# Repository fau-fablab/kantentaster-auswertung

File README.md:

kantentaster-auswertung
=======================

##motivation
Initially CNC mills do not "know" where the material is.
If you want to mill through the material, you have to know exactly where your material is relatively to the machine coordinate system.

For this the typical tool is a 3D probe.
However this probe cannot simply be connected to the controller of the mill.
This project is a Schmitt-triggered current loop to adapt the probe to the controller.

##circuit
The typical design for such a 3D probe (in our case a Renishaw) is that you have a contact which opens upon touching something with the tip of the probe.
When not touching anything the resistance of the probe is in the range of 20k.
When touching something the resistance becomes very large.

To have a robust measurement this circuit uses a current loop.
It consists of a constant-current-source which constantly puts a current of 1mA through the sensor.
Attached to this circuit is a Schmitt-trigger.
The hysteresis levels are configurable, because the trigger has to be fine tuned "in field".

Finally the output is separated from the controller with an optocoupler, because the sensor cable runs through a potentially rough environment.

----------------------
##version history
The first version of the PCB is in directory ```kantentaster_platine```. This version did not work. A complete redesign and current development version is in ```kantentaster_v2```.

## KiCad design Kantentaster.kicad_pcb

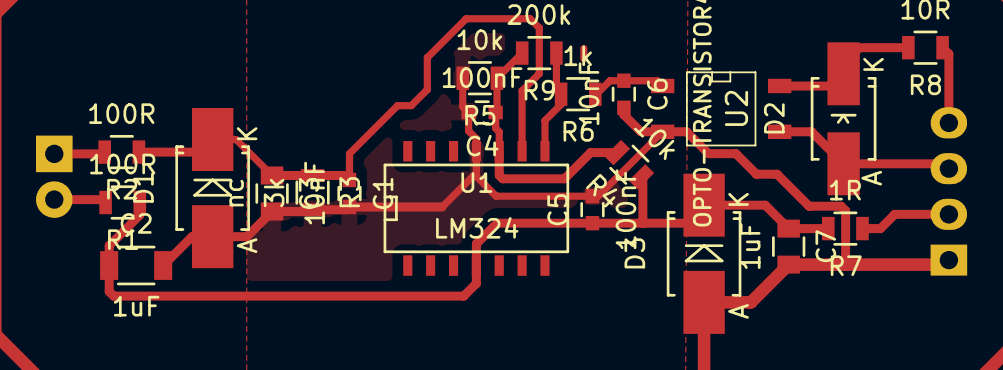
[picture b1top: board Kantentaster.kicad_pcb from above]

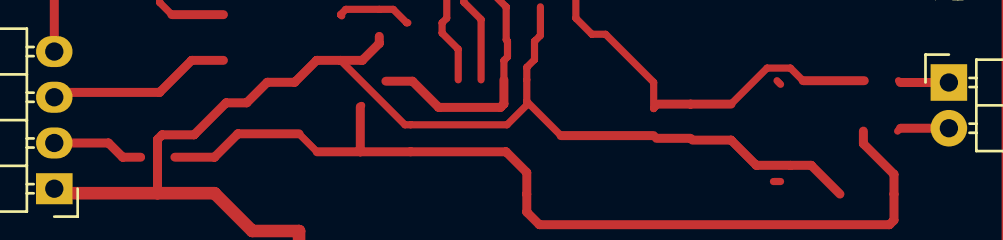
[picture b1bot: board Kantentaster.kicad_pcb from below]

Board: 2 copper layers, 23 parts (2 on the bottom side), 12 nets.

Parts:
C1, C6: 10nF; C_0603
C2: 1uF; C_1206
C3: nc; C_0805
C4, C5: 100nF; C_0603
C7: 1uF; C_0805
D1: ZENER_15V; Diode-SMB_Handsoldering
D2: ZENER_15V; Diode-SMA_Handsoldering
D3: ZENER_18V; Diode-SMB_Handsoldering
P1: Anschluss Kantentaster; Pin_Header_Angled_1x02
P2: CONN_01X04; Pin_Header_Angled_1x04
R1, R2: 100R; R_0805
R3: 3k; R_0805
R4, R5: 10k; R_0805
R6: 1k; R_0805
R7: 1R; R_0805
R8: 10R; R_0805
R9: 200k; R_0805
U1: LM324; SOIC-14_N
U2: OPTO-TRANSISTOR4; SO-4

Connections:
+12V: C2.1, C5.1, C7.1, D3.2, R1.1, R4.1, R7.2, U1.4
GND: C1.2, C2.2, C3.2, C4.2, C5.2, C6.2, C7.2, D1.1, D3.1, P2.1, R3.2, R5.2, U1.11, U2.2
unnamed: C1.1, C3.1, D1.2, R2.1, R3.1, U1.9
unnamed: C4.1, R4.2, R5.1, R9.2, U1.10
unnamed: C6.1, R6.1, U2.1
unnamed: D2.1, P2.3, U2.3
unnamed: D2.2, R8.2, U2.4
unnamed: P1.1, R2.2
unnamed: P1.2, R1.2
unnamed: P2.2, R7.1
unnamed: P2.4, R8.1
unnamed: R6.2, R9.1, U1.8

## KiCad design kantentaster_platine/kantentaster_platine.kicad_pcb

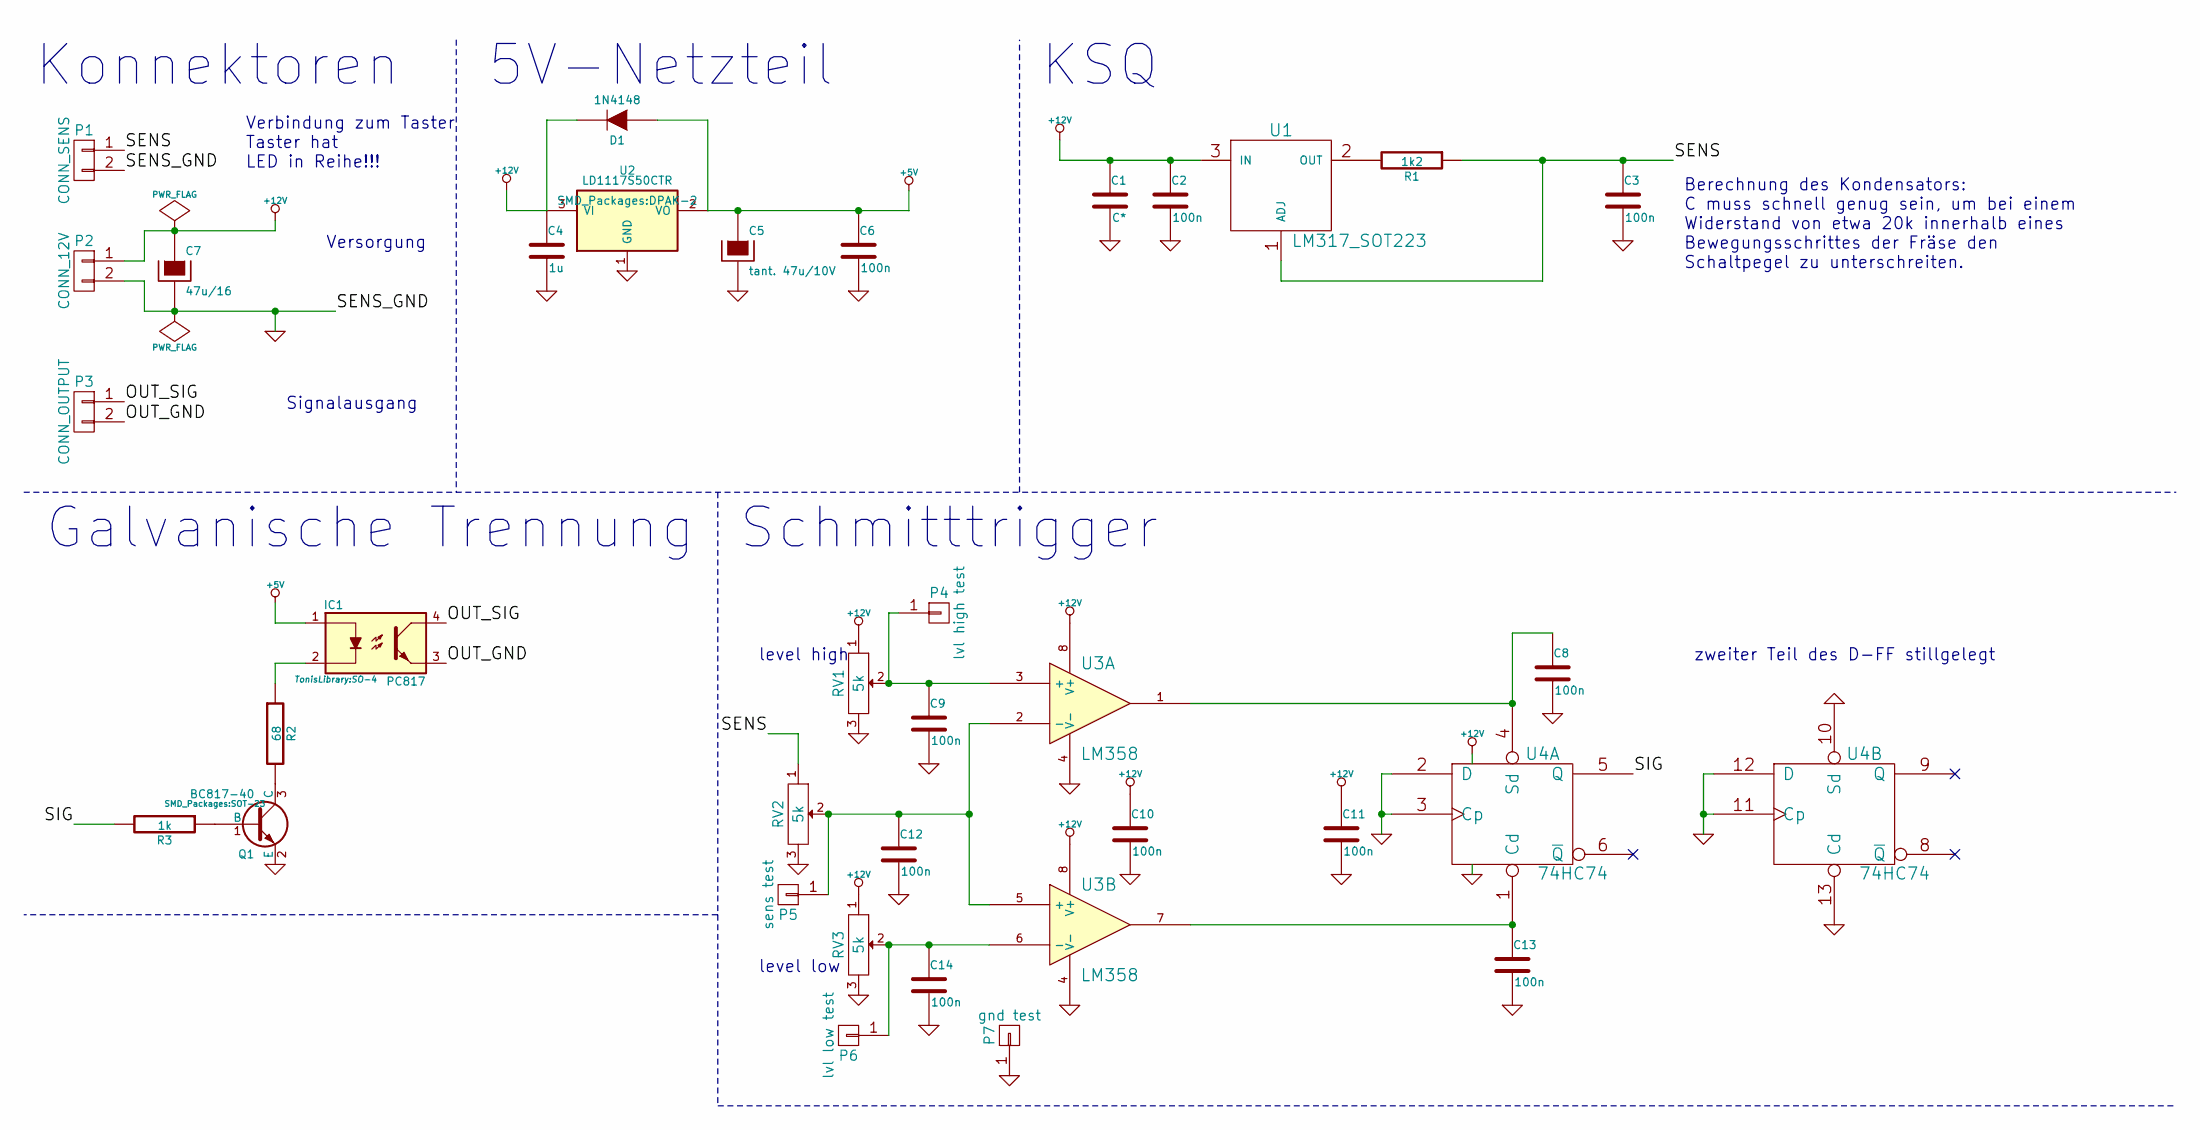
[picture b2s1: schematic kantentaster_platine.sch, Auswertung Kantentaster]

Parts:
C1: C*; C_0805
C2, C3, C6, C8, C9, C10, C11, C12, C13, C14: 100n; C_0805
C4: 1u; C_0805
C5: tant. 47u/10V; TantalC_SizeD_EIA-7343_Reflow
C7: 47u/16; c_elec_6.3x7.7
D1: 1N4148; Diode-MiniMELF_Standard
IC1: PC817; SO-4
P1: CONN_SENS; AK300-2
P2: CONN_12V; AK300-2
P3: CONN_OUTPUT; AK300-2
P4: lvl high test; Measurement_Point_Round-SMD-Pad_Big
P5: sens test; Measurement_Point_Round-SMD-Pad_Big
P6: lvl low test; Measurement_Point_Round-SMD-Pad_Big
P7: gnd test; Measurement_Point_Round-SMD-Pad_Big
Q1: BC817-40; SOT-23
R1: 1k2; SMD-0805
R2: 68; SMD-0805
R3: 1k; SMD-0805
RV1, RV2, RV3: 5k; Potentiometer_WirePads_Small
U1: LM317_SOT223; SOT-223
U2: LD1117S50CTR; DPAK-2
U3: LM358; DIP-8__300_ELL
U4: 74HC74; SOIC-14_W

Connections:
+5V: C5.1, C6.1, D1.1 (A), IC1.1, U2.2 (VO)
+12V: C1.1, C2.1, C4.1, C7.1, C10.1, C11.1, D1.2 (K), P2.1, RV1.1, RV3.1, U1.3 (IN), U2.3 (VI), U3.8 (V+), U4.14 (VCC)
/OUT_GND: IC1.3, P3.2
/OUT_SIG: IC1.4, P3.1
/SENS: C3.1, P1.1, R1.1, RV2.1, U1.1 (ADJ)
/SIG: R3.2, U4.5 (Q)
GND: C1.2, C2.2, C3.2, C4.2, C5.2, C6.2, C7.2, C8.2, C9.2, C10.2, C11.2, C12.2, C13.2, C14.2, P1.2, P2.2, P7.1, Q1.2 (E), RV1.3, RV2.3, RV3.3, U2.1 (GND), U3.4 (V-), U4.2 (D), U4.3 (Cp), U4.7 (GND), U4.10 (Sd), U4.11 (Cp), U4.12 (D), U4.13 (Cd)
unnamed: C8.1, U3.1, U4.4 (Sd)
unnamed: C9.1, P4.1, RV1.2, U3.3 (+)
unnamed: C12.1, P5.1, RV2.2, U3.2 (-), U3.5 (+)
unnamed: C13.1, U3.7, U4.1 (Cd)
unnamed: C14.1, P6.1, RV3.2, U3.6 (-)
unnamed: IC1.2, R2.1
unnamed: Q1.1 (B), R3.1
unnamed: Q1.3 (C), R2.2
unnamed: R1.2, U1.2 (OUT)

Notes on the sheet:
Konnektoren
5V-Netzteil
KSQ
Galvanische Trennung
Schmitttrigger
Verbindung zum Taster Taster hat LED in Reihe!!!
Versorgung
Signalausgang
level low
level high
zweiter Teil des D-FF stillgelegt
Berechnung des Kondensators: C muss schnell genug sein, um bei einem Widerstand von etwa 20k innerhalb eines Bewegungsschrittes der Fräse den Schaltpegel zu unterschreiten.

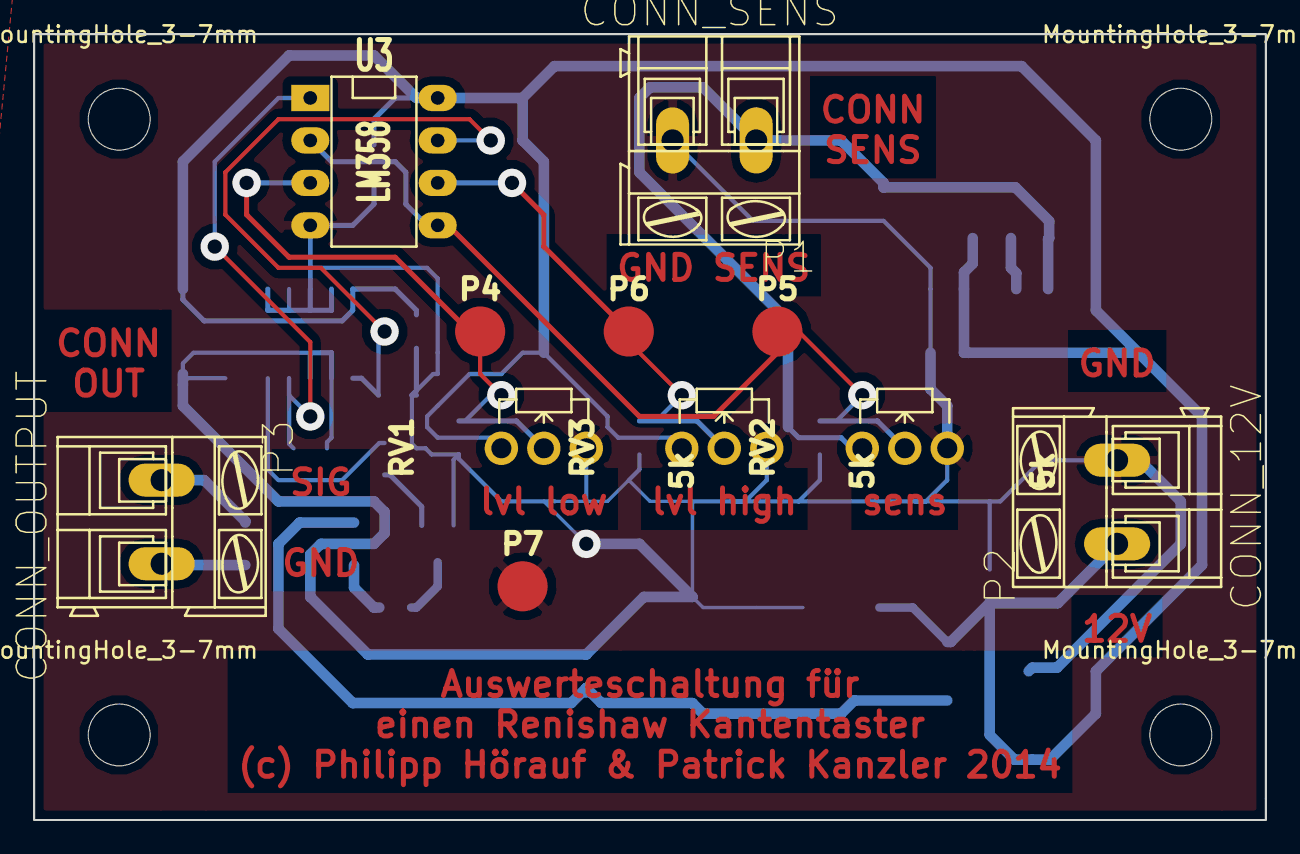
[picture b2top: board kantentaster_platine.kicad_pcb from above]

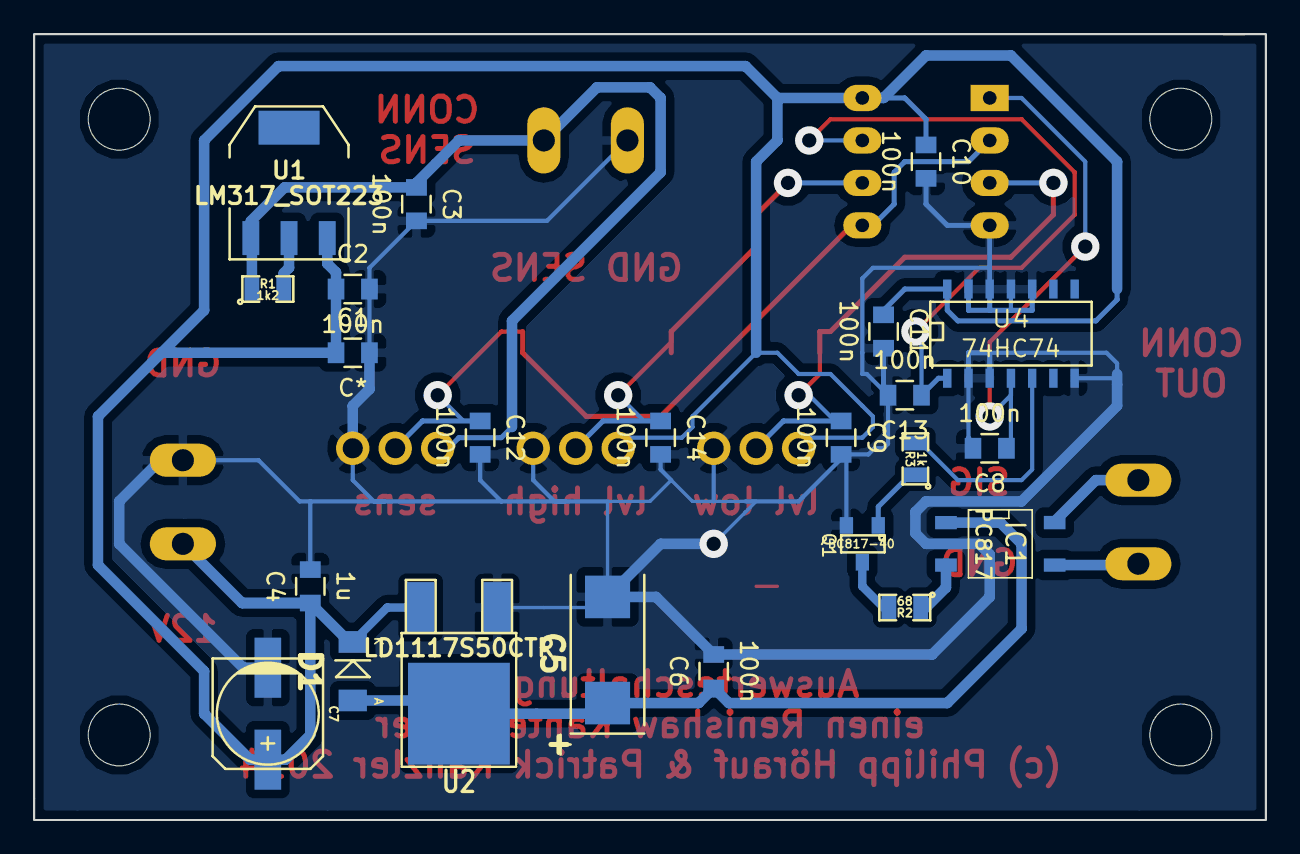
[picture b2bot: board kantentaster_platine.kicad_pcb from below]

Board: 2 copper layers, 73.7 x 47.0 mm, 38 parts (23 on the bottom side), 16 nets.

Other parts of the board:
MountingHole_3-7mm, MountingHole_3-7mm#2, MountingHole_3-7mm#3, MountingHole_3-7mm#4: VAL**; MountingHole_3-7mm

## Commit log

2014-12-01 Schaltplan für die Kantentaster-Auswertung
2014-12-10 alte Revisionen eingecheckt
2014-12-10 Designfiles eingecheckt
2014-12-10 Kleine Erläuterung gechrieben
2014-12-17 leiterbahn an messpad entfernt (optische Korrektur)
2015-02-14 Platine war Fail, TODO für nochmal machen ergänzt, wenn fertig mit neuen Bauteilen sauber aufbauen
2015-02-24 Projekt erstellt, Schaltplan fertig
2015-02-28 anpassungen am schaltplan und layout
2015-03-01 Mitkopplung hinzugefügt
2015-03-05 finale Version
2015-03-05 Fehler des ersten Prototypen behoben
2015-03-12 move layout by @ep092 into subfolder as preparation of merge
2015-03-12 update README considering merge
